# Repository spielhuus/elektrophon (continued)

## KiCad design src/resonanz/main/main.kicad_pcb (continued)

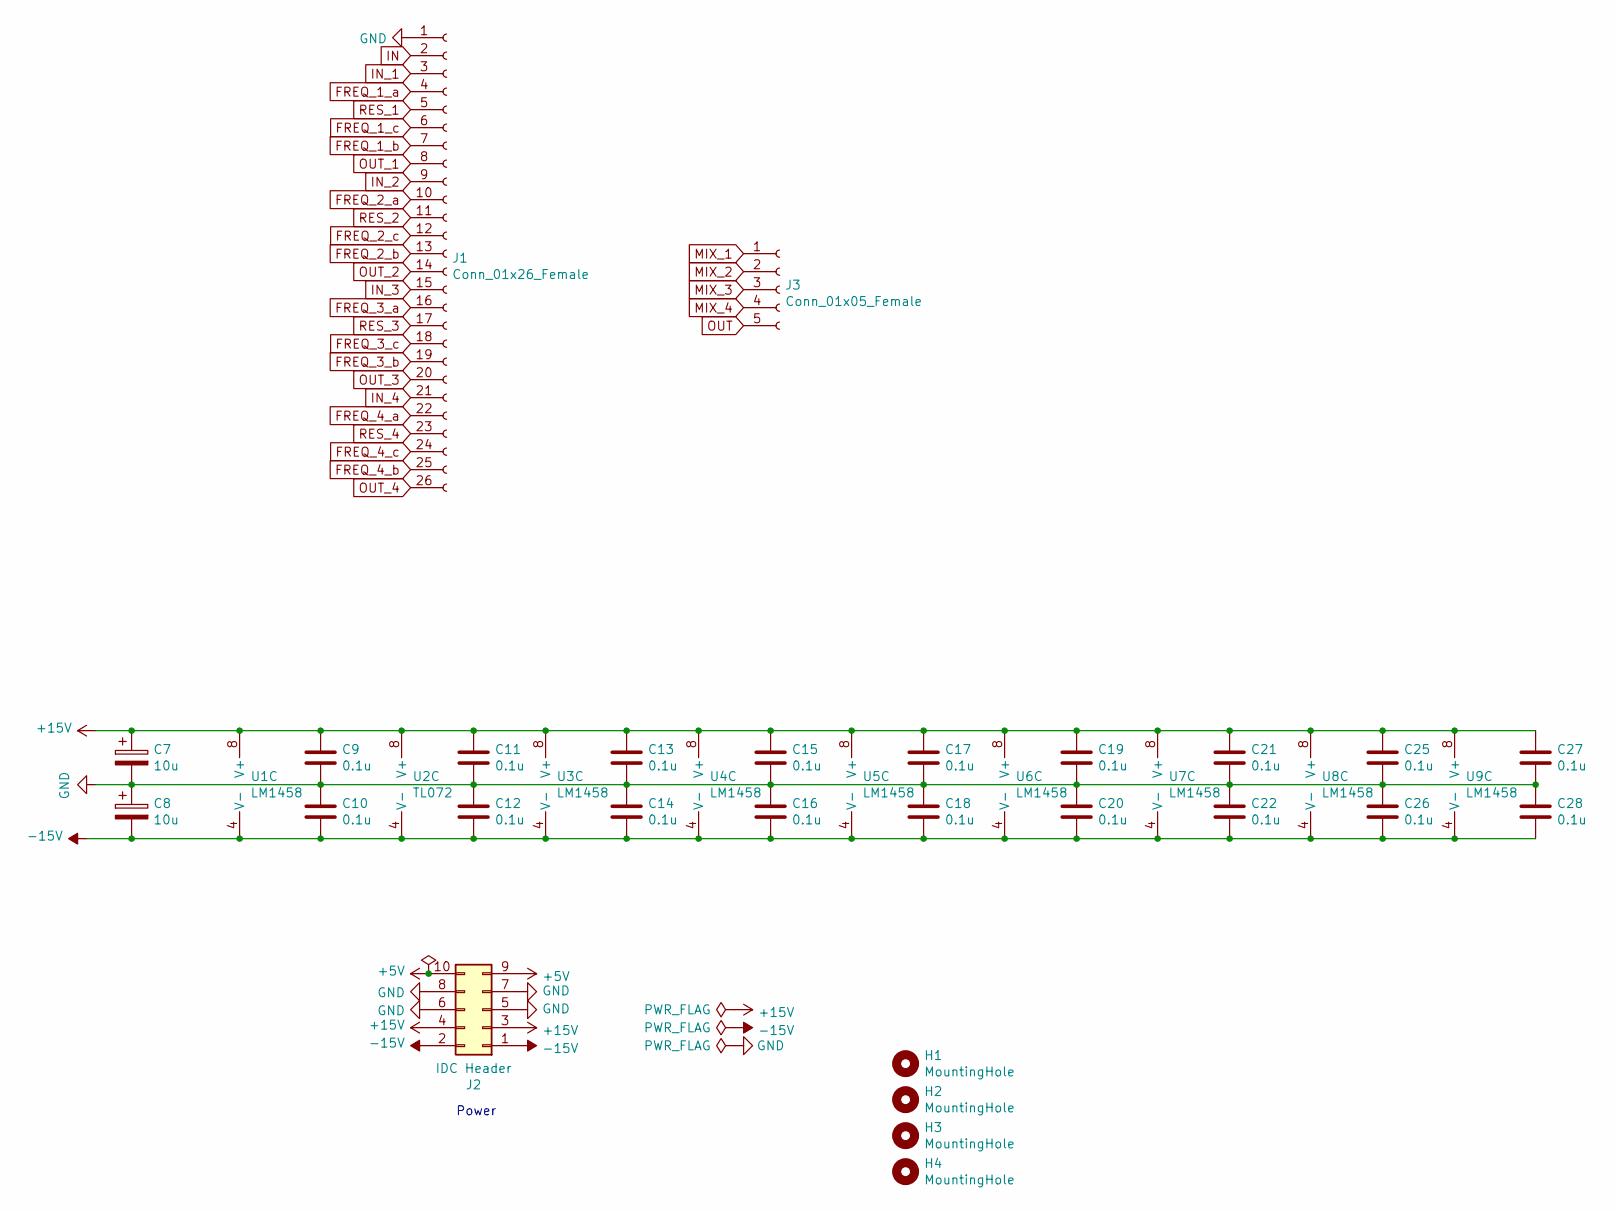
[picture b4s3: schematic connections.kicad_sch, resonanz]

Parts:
C7, C8: 10u; CP_Radial_D5.0mm_P2.50mm
C9, C10, C11, C12, C13, C14, C15, C16, C17, C18, C19, C20, C21, C22, C25, C26, C27, C28: 0.1u; C_Rect_L4.0mm_W2.5mm_P2.50mm
H1, H2, H3, H4: MountingHole; MountingHole_2.2mm_M2
J1: Conn_01x26_Female; PinHeader_1x26_P2.54mm_Vertical
J2: IDC Header; IDC-Header_2x05_P2.54mm_Vertical
J3: Conn_01x05_Female; PinHeader_1x05_P2.54mm_Vertical
U1, U3, U4, U5, U6, U7, U8, U9: LM1458; DIP-8_W7.62mm_Socket
U2: TL072; DIP-8_W7.62mm_Socket

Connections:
+5V: J2.9, J2.10
+15V: C7.1, C9.1, C11.1, C13.1, C15.1, C17.1, C19.1, C21.1, C25.1, C27.1, J2.3, J2.4, U1.8 (V+), U2.8 (V+), U3.8 (V+), U4.8 (V+), U5.8 (V+), U6.8 (V+), U7.8 (V+), U8.8 (V+), U9.8 (V+)
-15V: C8.2, C10.2, C12.2, C14.2, C16.2, C18.2, C20.2, C22.2, C26.2, C28.2, J2.1, J2.2, U1.4 (V-), U2.4 (V-), U3.4 (V-), U4.4 (V-), U5.4 (V-), U6.4 (V-), U7.4 (V-), U8.4 (V-), U9.4 (V-)
FREQ_1_a: J1.4; also elsewhere on the board
FREQ_1_b: J1.7; also elsewhere on the board
FREQ_1_c: J1.6; also elsewhere on the board
FREQ_2_a: J1.10; also elsewhere on the board
FREQ_2_b: J1.13; also elsewhere on the board
FREQ_2_c: J1.12; also elsewhere on the board
FREQ_3_a: J1.16; also elsewhere on the board
FREQ_3_b: J1.19; also elsewhere on the board
FREQ_3_c: J1.18; also elsewhere on the board
FREQ_4_a: J1.22; also elsewhere on the board
FREQ_4_b: J1.25; also elsewhere on the board
FREQ_4_c: J1.24; also elsewhere on the board
GND: C7.2, C8.1, C9.2, C10.1, C11.2, C12.1, C13.2, C14.1, C15.2, C16.1, C17.2, C18.1, C19.2, C20.1, C21.2, C22.1, C25.2, C26.1, C27.2, C28.1, J1.1, J2.5, J2.6, J2.7, J2.8; also elsewhere on the board
IN: J1.2; also elsewhere on the board
IN_1: J1.3; also elsewhere on the board
IN_2: J1.9; also elsewhere on the board
IN_3: J1.15; also elsewhere on the board
IN_4: J1.21; also elsewhere on the board
MIX_1: J3.1; also elsewhere on the board
MIX_2: J3.2; also elsewhere on the board
MIX_3: J3.3; also elsewhere on the board
MIX_4: J3.4; also elsewhere on the board
OUT: J3.5; also elsewhere on the board
OUT_1: J1.8; also elsewhere on the board
OUT_2: J1.14; also elsewhere on the board
OUT_3: J1.20; also elsewhere on the board
OUT_4: J1.26; also elsewhere on the board
RES_1: J1.5; also elsewhere on the board
RES_2: J1.11; also elsewhere on the board
RES_3: J1.17; also elsewhere on the board
RES_4: J1.23; also elsewhere on the board

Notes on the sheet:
Power

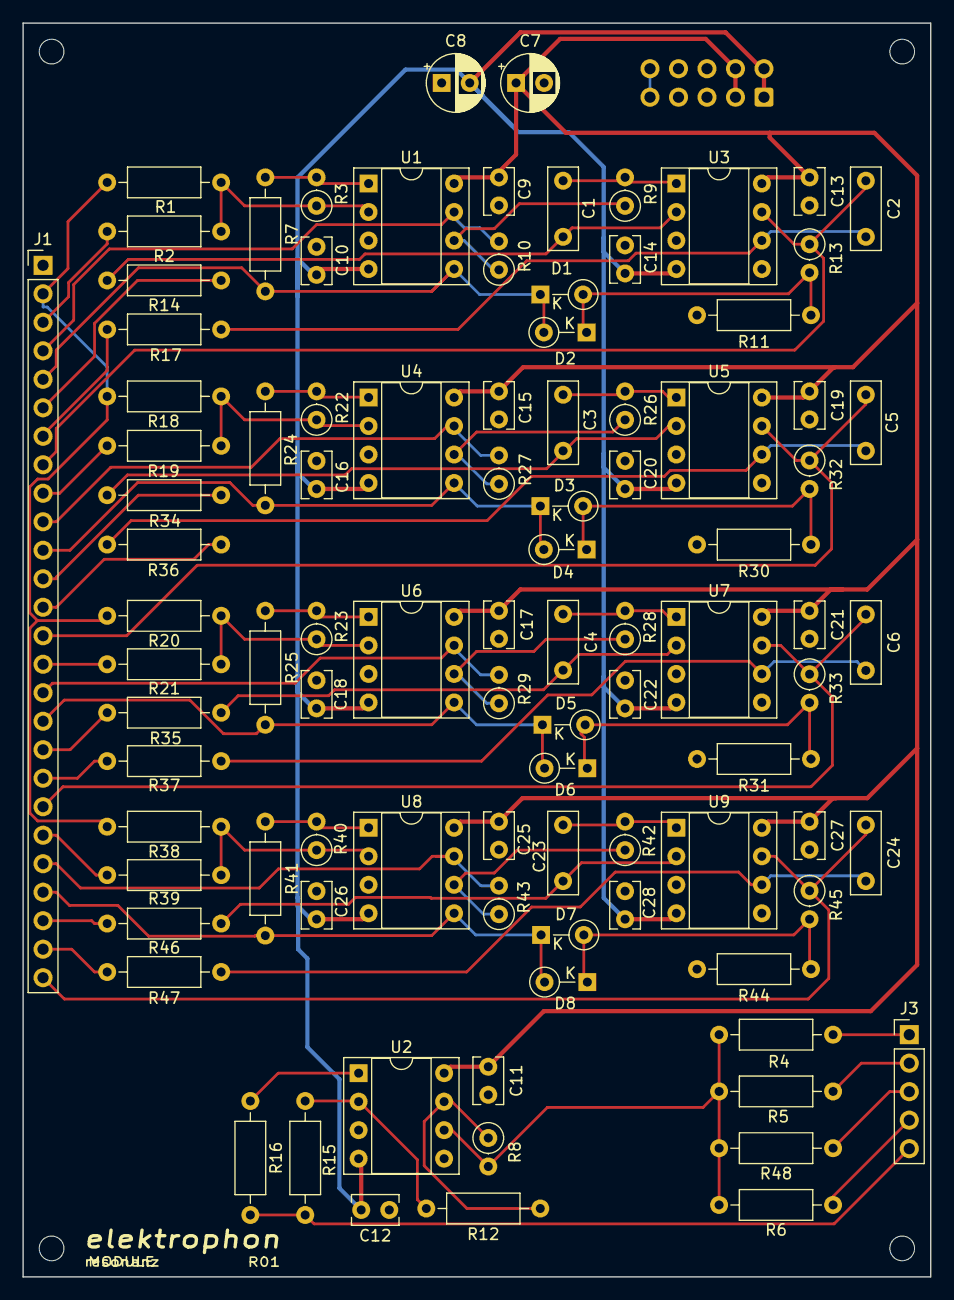
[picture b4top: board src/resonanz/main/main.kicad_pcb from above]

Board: 2 copper layers, 80.9 x 111.8 mm, 101 parts (1 on the bottom side), 66 nets.

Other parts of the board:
REF1: elektrophon logo

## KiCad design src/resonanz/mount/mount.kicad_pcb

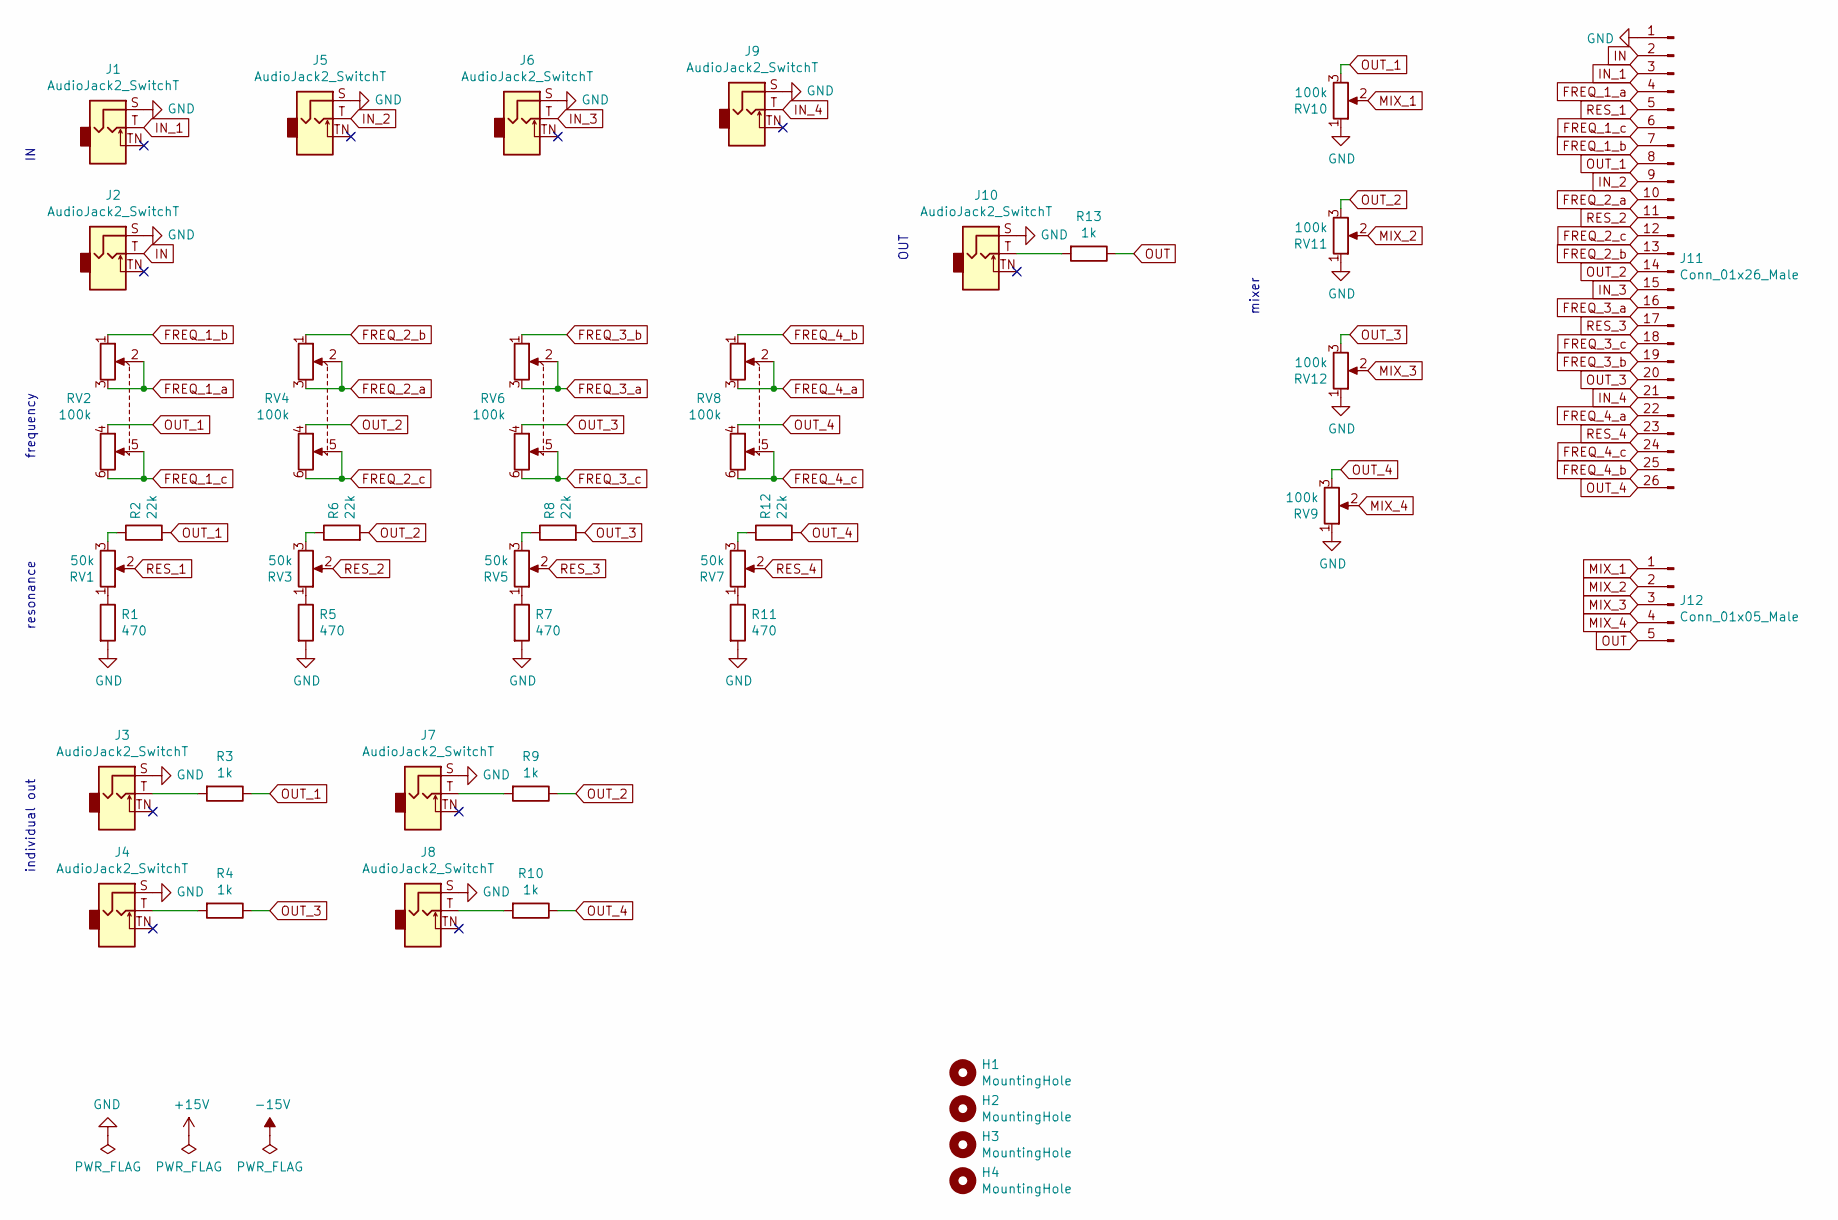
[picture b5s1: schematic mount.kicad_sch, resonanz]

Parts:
H1, H2, H3, H4: MountingHole; MountingHole_2.2mm_M2
J1, J2, J3, J4, J5, J6, J7, J8, J9, J10: AudioJack2_SwitchT; Jack_3.5mm_WQP-PJ398SM_Vertical
J11: Conn_01x26_Male; PinHeader_1x26_P2.54mm_Vertical
J12: Conn_01x05_Male; PinHeader_1x05_P2.54mm_Vertical
R1, R5, R7, R11: 470; R_Axial_DIN0207_L6.3mm_D2.5mm_P10.16mm_Horizontal
R2, R6, R8, R12: 22k; R_Axial_DIN0207_L6.3mm_D2.5mm_P10.16mm_Horizontal
R3, R4, R9, R10, R13: 1k; R_Axial_DIN0207_L6.3mm_D2.5mm_P10.16mm_Horizontal
RV1, RV3, RV5, RV7: 50k; Potentiometer_Alpha_RD901F-40-00D_Single_Vertical
RV2, RV4, RV6, RV8: 100k; Potentiometer_Alpha_RD902F-40-00D_Dual_Vertical
RV9, RV10, RV11, RV12: 100k; Potentiometer_Alpha_RD901F-40-00D_Single_Vertical

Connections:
FREQ_1_a: J11.4, RV2.2, RV2.3
FREQ_1_b: J11.7, RV2.1
FREQ_1_c: J11.6, RV2.5, RV2.6
FREQ_2_a: J11.10, RV4.2, RV4.3
FREQ_2_b: J11.13, RV4.1
FREQ_2_c: J11.12, RV4.5, RV4.6
FREQ_3_a: J11.16, RV6.2, RV6.3
FREQ_3_b: J11.19, RV6.1
FREQ_3_c: J11.18, RV6.5, RV6.6
FREQ_4_a: J11.22, RV8.2, RV8.3
FREQ_4_b: J11.25, RV8.1
FREQ_4_c: J11.24, RV8.5, RV8.6
GND: J1.S, J2.S, J3.S, J4.S, J5.S, J6.S, J7.S, J8.S, J9.S, J10.S, J11.1, R1.2, R5.2, R7.2, R11.2, RV9.1, RV10.1, RV11.1, RV12.1
IN: J2.T, J11.2
IN_1: J1.T, J11.3
IN_2: J5.T, J11.9
IN_3: J6.T, J11.15
IN_4: J9.T, J11.21
MIX_1: J12.1, RV10.2
MIX_2: J12.2, RV11.2
MIX_3: J12.3, RV12.2
MIX_4: J12.4, RV9.2
unnamed: J3.T, R3.2
unnamed: J4.T, R4.2
unnamed: J7.T, R9.2
unnamed: J8.T, R10.2
unnamed: J10.T, R13.2
unnamed: R1.1, RV1.1
unnamed: R2.1, RV1.3
unnamed: R5.1, RV3.1
unnamed: R6.1, RV3.3
unnamed: R7.1, RV5.1
unnamed: R8.1, RV5.3
unnamed: R11.1, RV7.1
unnamed: R12.1, RV7.3
OUT: J12.5, R13.1
OUT_1: J11.8, R2.2, R3.1, RV2.4, RV10.3
OUT_2: J11.14, R6.2, R9.1, RV4.4, RV11.3
OUT_3: J11.20, R4.1, R8.2, RV6.4, RV12.3
OUT_4: J11.26, R10.1, R12.2, RV8.4, RV9.3
RES_1: J11.5, RV1.2
RES_2: J11.11, RV3.2
RES_3: J11.17, RV5.2
RES_4: J11.23, RV7.2

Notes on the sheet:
resonance
individual out
mixer
OUT
frequency

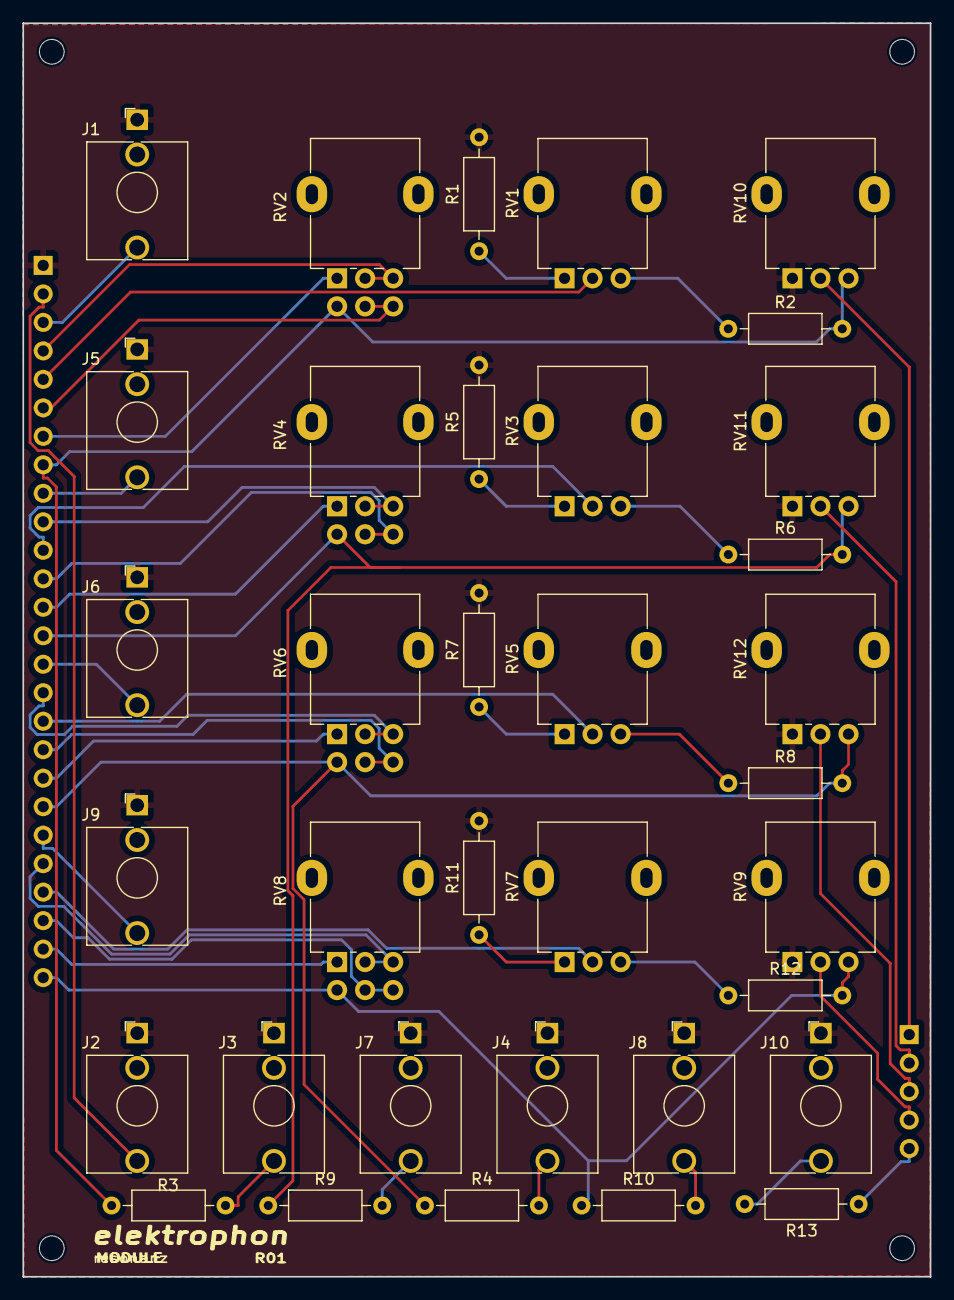
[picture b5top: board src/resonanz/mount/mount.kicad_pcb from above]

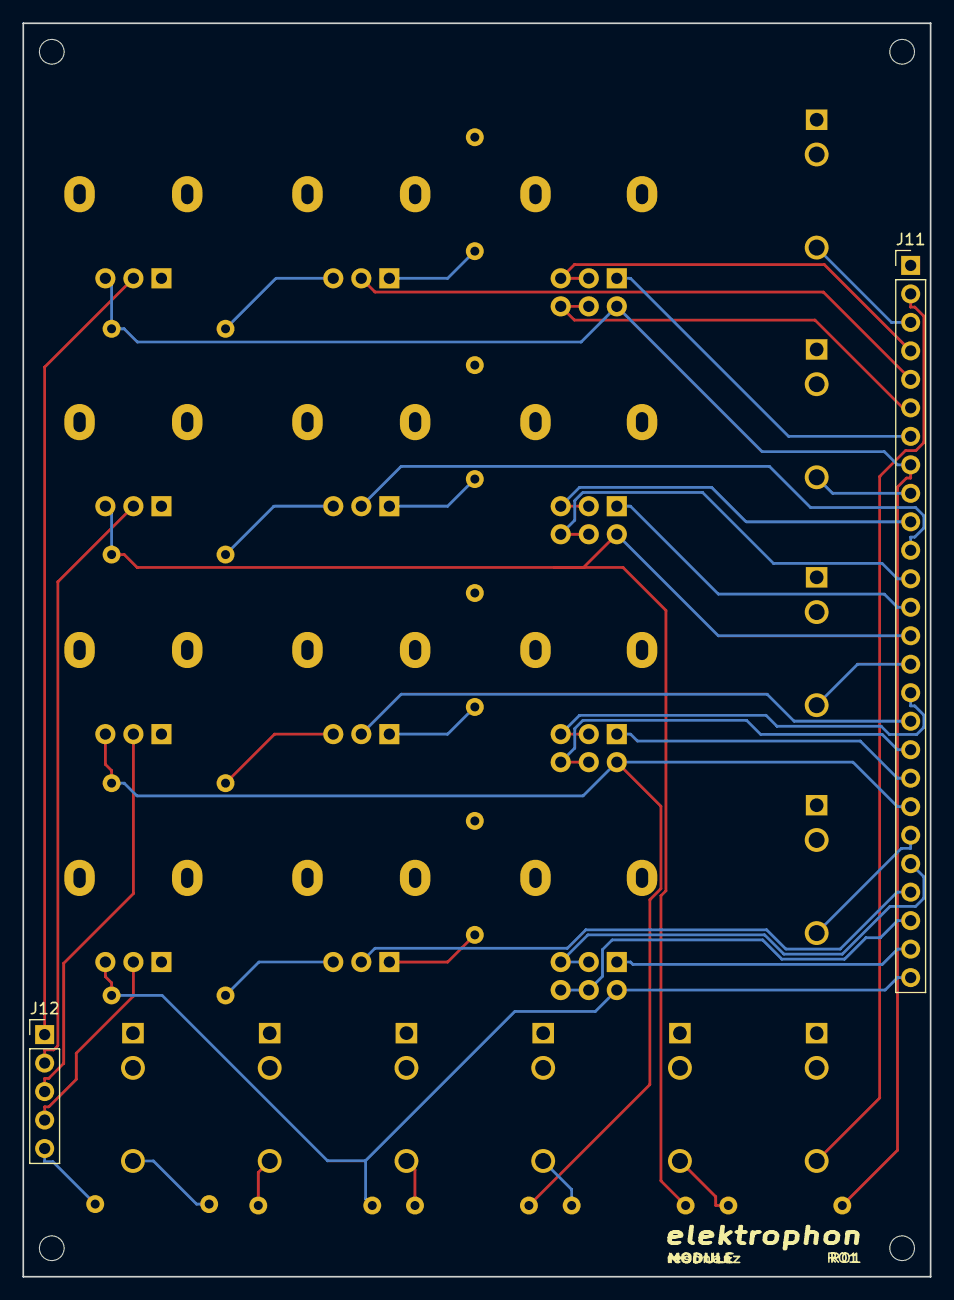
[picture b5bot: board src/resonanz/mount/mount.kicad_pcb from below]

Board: 2 copper layers, 80.9 x 111.8 mm, 41 parts (2 on the bottom side), 44 nets.

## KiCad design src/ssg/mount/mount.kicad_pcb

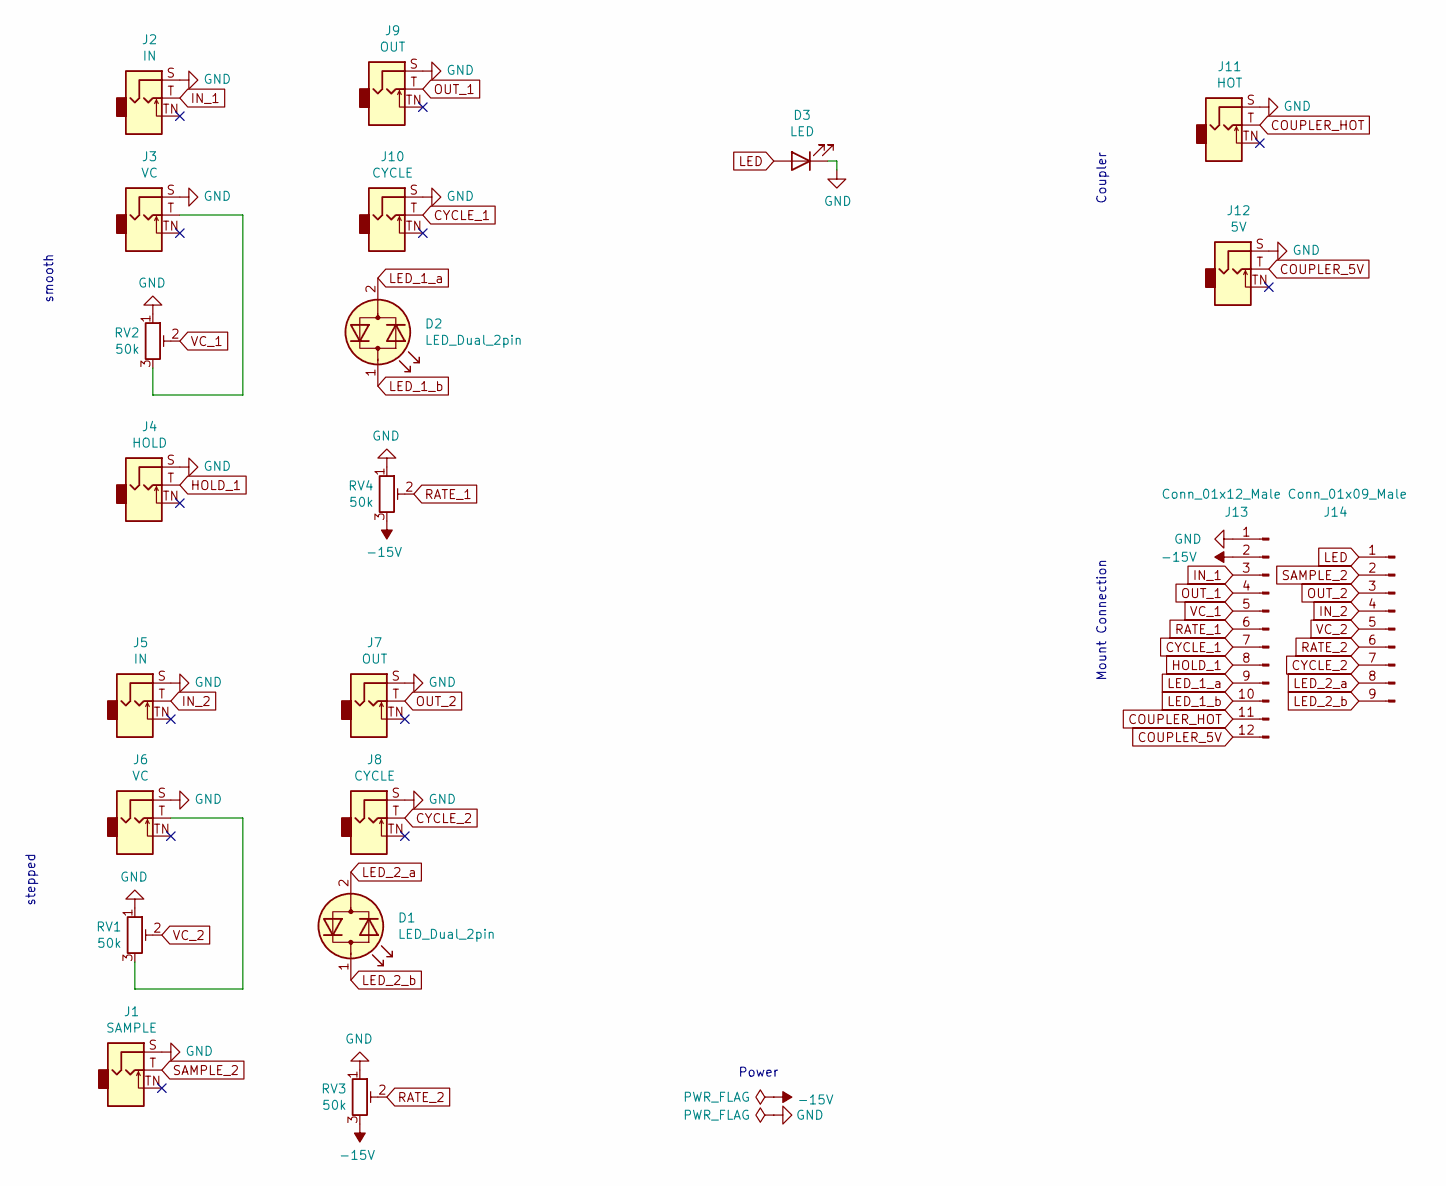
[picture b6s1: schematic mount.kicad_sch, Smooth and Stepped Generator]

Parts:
D1, D2: LED_Dual_2pin; LED_D5.0mm
D3: LED; LED_D5.0mm
J1: SAMPLE; Jack_3.5mm_WQP-PJ398SM_Vertical
J2, J5: IN; Jack_3.5mm_WQP-PJ398SM_Vertical
J3, J6: VC; Jack_3.5mm_WQP-PJ398SM_Vertical
J4: HOLD; Jack_3.5mm_WQP-PJ398SM_Vertical
J7, J9: OUT; Jack_3.5mm_WQP-PJ398SM_Vertical
J8, J10: CYCLE; Jack_3.5mm_WQP-PJ398SM_Vertical
J11: HOT; Jack_3.5mm_WQP-PJ398SM_Vertical
J12: 5V; Jack_3.5mm_WQP-PJ398SM_Vertical
J13: Conn_01x12_Male; PinHeader_1x12_P2.54mm_Vertical
J14: Conn_01x09_Male; PinHeader_1x09_P2.54mm_Vertical
RV1, RV2, RV3, RV4: 50k; Potentiometer_Alpha_RD901F-40-00D_Single_Vertical

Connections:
-15V: J13.2, RV3.3, RV4.3
COUPLER_5V: J12.T, J13.12
COUPLER_HOT: J11.T, J13.11
CYCLE_1: J10.T, J13.7
CYCLE_2: J8.T, J14.7
GND: D3.1 (K), J1.S, J2.S, J3.S, J4.S, J5.S, J6.S, J7.S, J8.S, J9.S, J10.S, J11.S, J12.S, J13.1, RV1.1, RV2.1, RV3.1, RV4.1
HOLD_1: J4.T, J13.8
IN_1: J2.T, J13.3
IN_2: J5.T, J14.4
LED: D3.2 (A), J14.1
LED_1_a: D2.2 (AK), J13.9
LED_1_b: D2.1 (KA), J13.10
LED_2_a: D1.2 (AK), J14.8
LED_2_b: D1.1 (KA), J14.9
unnamed: J3.T, RV2.3
unnamed: J6.T, RV1.3
OUT_1: J9.T, J13.4
OUT_2: J7.T, J14.3
RATE_1: J13.6, RV4.2
RATE_2: J14.6, RV3.2
SAMPLE_2: J1.T, J14.2
VC_1: J13.5, RV2.2
VC_2: J14.5, RV1.2

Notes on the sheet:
stepped
Coupler
Mount Connection
Power
smooth

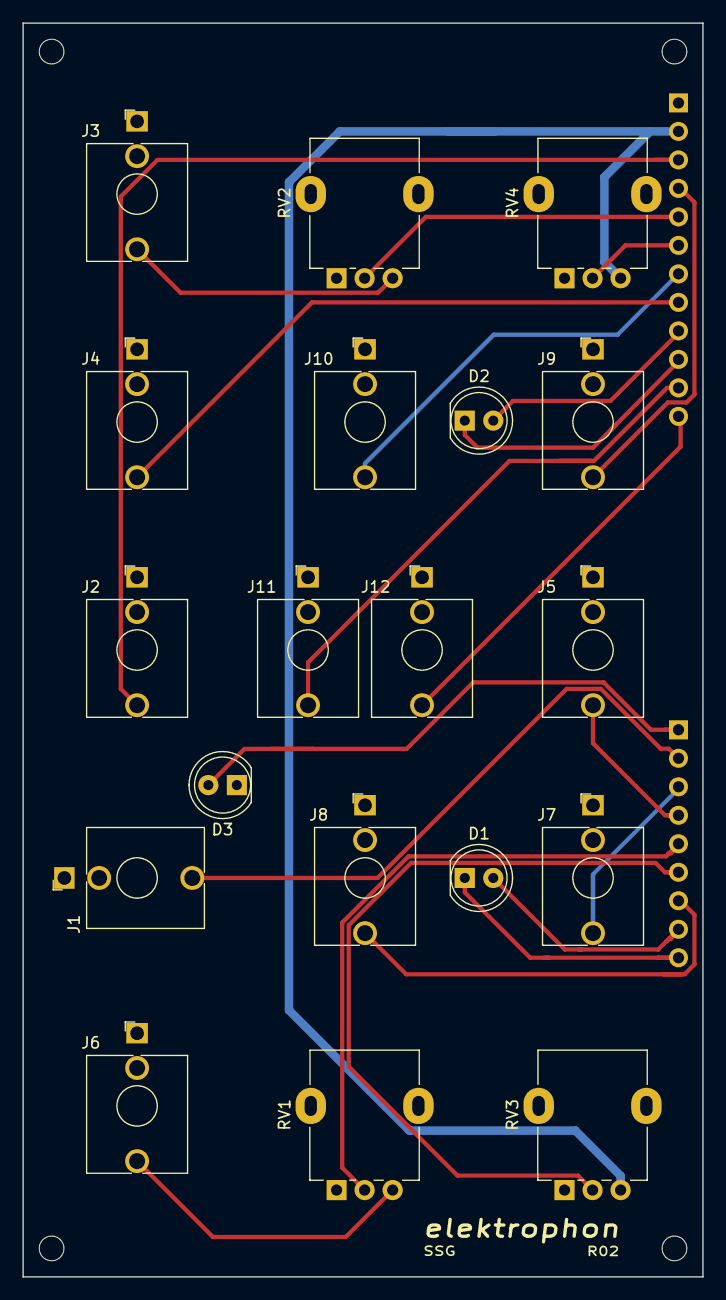
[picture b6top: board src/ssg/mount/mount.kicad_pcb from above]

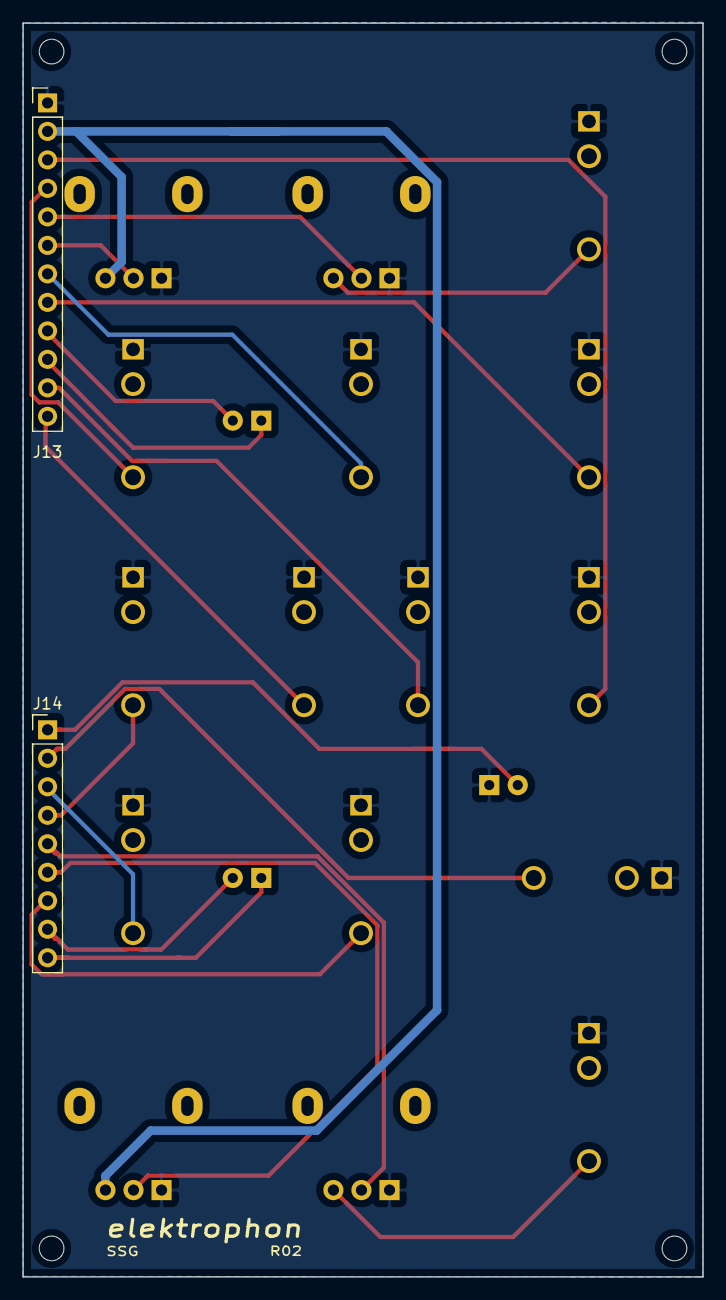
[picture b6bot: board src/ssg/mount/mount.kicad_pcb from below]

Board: 2 copper layers, 60.6 x 111.8 mm, 21 parts (2 on the bottom side), 23 nets.
